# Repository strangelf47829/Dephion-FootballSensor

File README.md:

# Dephion FootballSensor
 
NOT IN PUBLIC DOMAIN!!!!

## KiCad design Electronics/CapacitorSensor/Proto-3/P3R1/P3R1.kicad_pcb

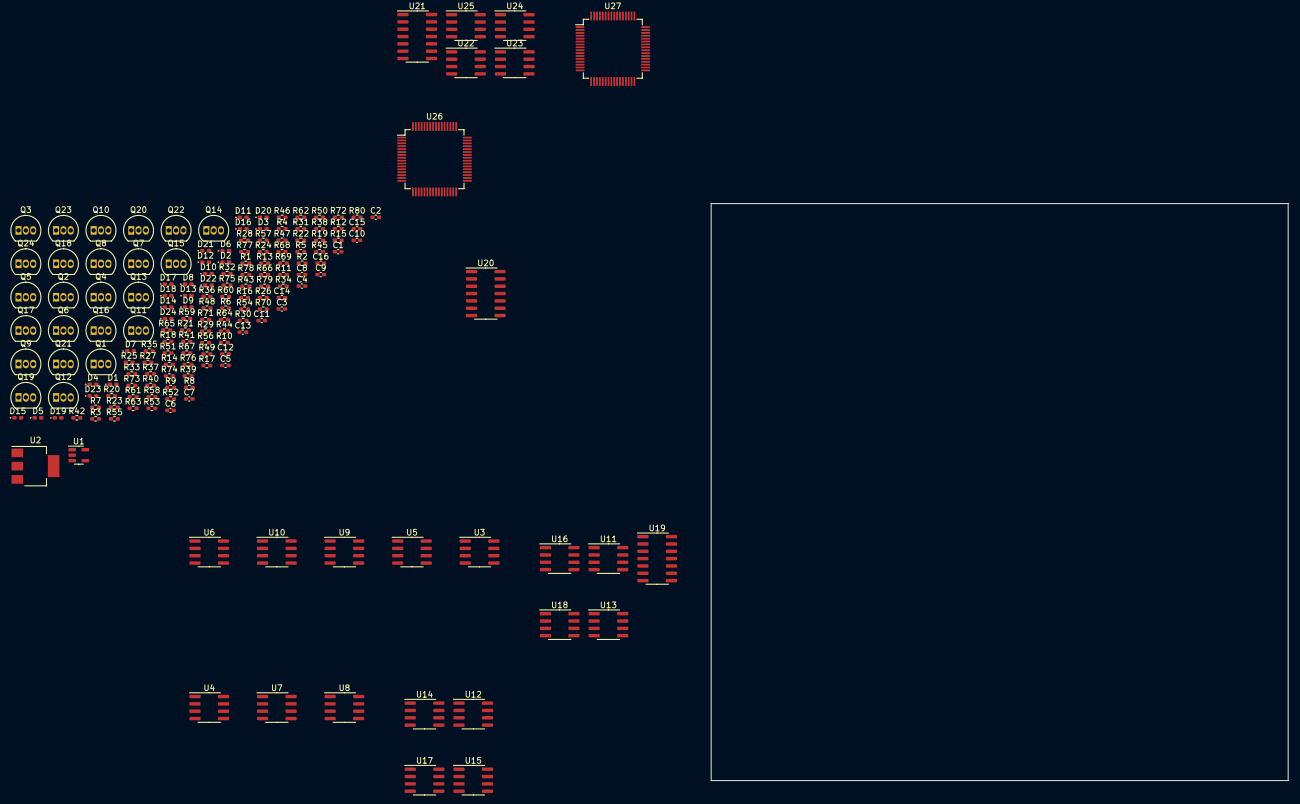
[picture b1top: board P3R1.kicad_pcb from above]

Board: 2 copper layers, 100.0 x 100.0 mm, 171 parts (0 on the bottom side), 124 nets, no tracks yet.

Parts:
C1, C2, C3, C4, C5, C6, C7, C8, C9, C10, C11, C12, C13, C14, C15, C16: C; C_0402_1005Metric_Pad0.74x0.62mm_HandSolder
D1, D2, D3, D4, D5, D6, D7, D8, D9, D10, D11, D12, D13, D14, D15, D16, D17, D18, D19, D20, D21, D22, D23, D24: D; D_0402_1005Metric_Pad0.77x0.64mm_HandSolder
Q1, Q2, Q3, Q4, Q5, Q6, Q7, Q8, Q17, Q18, Q19, Q20, Q21, Q22, Q23, Q24: BC547; TO-92_Inline
Q9, Q10, Q11, Q12, Q13, Q14, Q15, Q16: BS107; TO-92_Inline
R1, R2, R3, R4, R5, R6, R7, R8, R9, R10, R11, R12, R13, R14, R15, R16, R17, R18, R19, R20, R21, R22, R23, R24, R25, R26, R27, R28, R29, R30, R31, R32, R33, R34, R35, R36, R37, R38, R39, R40, R41, R42, R43, R44, R45, R46, R47, R48, R49, R50, R51, R52, R53, R54, R55, R56, R57, R58, R59, R60, R61, R62, R63, R64, R65, R66, R67, R68, R69, R70, R71, R72, R73, R74, R75, R76, R77, R78, R79, R80: R; R_0402_1005Metric_Pad0.72x0.64mm_HandSolder
U1: TC2185-2.8VxCTTR; SOT-23-5
U2: AMS1117-5.0; SOT-223-3_TabPin2
U3, U4, U5, U6, U7, U8, U9, U10, U11, U12, U13, U14, U15, U16, U17, U18: LM318N; SOIC-8_3.9x4.9mm_P1.27mm
U19, U20, U21: 74LS14; SOIC-14_3.9x8.7mm_P1.27mm
U22, U23, U24, U25: LM393; SOIC-8_3.9x4.9mm_P1.27mm
U26, U27: STM32L431RCTx; LQFP-64_10x10mm_P0.5mm

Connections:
+2V8: R42.1, R44.1, R46.1, R48.1, R50.1, R52.1, R54.1, R56.1
+5V: U22.8 (V+), U23.8 (V+), U24.8 (V+), U25.8 (V+)
B0: Q1.3 (E), Q9.1 (D), Q17.3 (E), R41.2, U3.3 (+), U3.4 (V-), U11.4 (V-)
B1: Q2.3 (E), Q10.1 (D), Q18.3 (E), R43.2, U4.3 (+), U4.4 (V-), U12.4 (V-)
B2: Q3.3 (E), Q11.1 (D), Q19.3 (E), R45.2, U5.3 (+), U5.4 (V-), U13.4 (V-)
B3: Q4.3 (E), Q12.1 (D), Q20.3 (E), R47.2, U6.3 (+), U6.4 (V-), U14.4 (V-)
B4: Q5.3 (E), Q13.1 (D), Q21.3 (E), R49.2, U7.3 (+), U7.4 (V-), U15.4 (V-)
B5: Q6.3 (E), Q14.1 (D), Q22.3 (E), R51.2, U8.3 (+), U8.4 (V-), U16.4 (V-)
B6: Q7.3 (E), Q15.1 (D), Q23.3 (E), R53.2, U9.3 (+), U9.4 (V-), U17.4 (V-)
B7: Q8.3 (E), Q16.1 (D), Q24.3 (E), R55.2, U10.3 (+), U10.4 (V-), U18.4 (V-)
C0: D1.2 (A), R1.1
C1: D2.2 (A), R2.1
C2: D3.2 (A), R3.1
C3: D4.2 (A), R4.1
C4: D5.2 (A), R5.1
C5: D6.2 (A), R6.1
C6: D7.2 (A), R7.1
C7: D8.2 (A), R8.1
G0: D1.1 (K), D9.2 (A)
G1: D2.1 (K), D10.2 (A)
G2: D3.1 (K), D11.2 (A)
G3: D4.1 (K), D12.2 (A)
G4: D5.1 (K), D13.2 (A)
G5: D6.1 (K), D14.2 (A)
G6: D7.1 (K), D15.2 (A)
G7: D8.1 (K), D16.2 (A)
GNDA: U22.3 (+), U22.4 (V-), U22.5 (+), U23.3 (+), U23.4 (V-), U23.5 (+), U24.3 (+), U24.4 (V-), U24.5 (+), U25.3 (+), U25.4 (V-), U25.5 (+)
unnamed: C1.1, R25.2
unnamed: C1.2, C9.2, R33.1, U3.2 (-)
unnamed: C2.1, R26.2
unnamed: C3.1, R27.2
unnamed: C4.1, R28.2
unnamed: C5.1, R29.2
unnamed: C6.1, R30.2
unnamed: C7.1, R31.2
unnamed: C8.1, R32.2
unnamed: C9.1, D17.1 (K), R33.2, R65.2
unnamed: C10.1, D18.1 (K), R34.2, R66.2, U4.8 (BAL2)
unnamed: C2.2, C10.2, R34.1, U4.2 (-)
unnamed: C11.1, D19.1 (K), R35.2, R67.2, U5.8 (BAL2)
unnamed: C3.2, C11.2, R35.1, U5.2 (-)
unnamed: C12.1, D20.1 (K), R36.2, R68.2, U6.8 (BAL2)
unnamed: C4.2, C12.2, R36.1, U6.2 (-)
unnamed: C13.1, D21.1 (K), R37.2, R69.2, U7.8 (BAL2)
unnamed: C5.2, C13.2, R37.1, U7.2 (-)
unnamed: C14.1, D22.1 (K), R38.2, R70.2, U8.8 (BAL2)
unnamed: C6.2, C14.2, R38.1, U8.2 (-)
unnamed: C15.1, D23.1 (K), R39.2, R71.2, U9.8 (BAL2)
unnamed: C7.2, C15.2, R39.1, U9.2 (-)
unnamed: C16.1, D24.1 (K), R40.2, R72.2, U10.8 (BAL2)
unnamed: C8.2, C16.2, R40.1, U10.2 (-)
unnamed: D9.1 (K), R17.1
unnamed: D10.1 (K), R18.1
unnamed: D11.1 (K), R19.1
unnamed: D12.1 (K), R20.1
unnamed: D13.1 (K), R21.1
unnamed: D14.1 (K), R22.1
unnamed: D15.1 (K), R23.1
unnamed: D16.1 (K), R24.1
unnamed: D17.2 (A), Q17.1 (C), R73.2, U11.6, U19.1
unnamed: D18.2 (A), Q18.1 (C), R74.2, U12.6, U19.5
unnamed: D19.2 (A), Q19.1 (C), R75.2, U13.6, U19.11
unnamed: D20.2 (A), Q20.1 (C), R76.2, U14.6, U20.1
unnamed: D21.2 (A), Q21.1 (C), R77.2, U15.6, U20.5
unnamed: D22.2 (A), Q22.1 (C), R78.2, U16.6, U20.11
unnamed: D23.2 (A), Q23.1 (C), R79.2, U17.6, U21.1
unnamed: D24.2 (A), Q24.1 (C), R80.2, U18.6, U21.5
unnamed: Q1.1 (C), Q9.2 (G), R9.2
unnamed: Q1.2 (B), R1.2
unnamed: Q2.2 (B), R2.2
unnamed: Q3.2 (B), R3.2
unnamed: Q4.2 (B), R4.2
unnamed: Q5.2 (B), R5.2
unnamed: Q6.2 (B), R6.2
unnamed: Q7.2 (B), R7.2
unnamed: Q8.2 (B), R8.2
unnamed: Q9.3 (S), R17.2, R25.1
unnamed: Q2.1 (C), Q10.2 (G), R10.2
unnamed: Q10.3 (S), R18.2, R26.1
unnamed: Q3.1 (C), Q11.2 (G), R11.2
unnamed: Q11.3 (S), R19.2, R27.1
unnamed: Q4.1 (C), Q12.2 (G), R12.2
unnamed: Q12.3 (S), R20.2, R28.1
unnamed: Q5.1 (C), Q13.2 (G), R13.2
unnamed: Q13.3 (S), R21.2, R29.1
unnamed: Q6.1 (C), Q14.2 (G), R14.2
unnamed: Q14.3 (S), R22.2, R30.1
unnamed: Q7.1 (C), Q15.2 (G), R15.2
unnamed: Q15.3 (S), R23.2, R31.1
unnamed: Q8.1 (C), Q16.2 (G), R16.2
unnamed: Q16.3 (S), R24.2, R32.1
unnamed: R41.1, R42.2, R57.1
unnamed: R43.1, R44.2, R58.1
unnamed: R45.1, R46.2, R59.1
unnamed: R47.1, R48.2, R60.1
unnamed: R49.1, R50.2, R61.1
unnamed: R51.1, R52.2, R62.1
unnamed: R53.1, R54.2, R63.1
unnamed: R55.1, R56.2, R64.1
unnamed: R57.2, R73.1
unnamed: R58.2, R74.1
unnamed: R59.2, R75.1
unnamed: R60.2, R76.1
unnamed: R61.2, R77.1
unnamed: R62.2, R78.1
unnamed: R63.2, R79.1
unnamed: R64.2, R80.1
unnamed: R65.1, U11.3 (+)
unnamed: R66.1, U12.3 (+)
unnamed: R67.1, U13.3 (+)
unnamed: R68.1, U14.3 (+)
unnamed: R69.1, U15.3 (+)
unnamed: R70.1, U16.3 (+)
unnamed: R71.1, U17.3 (+)
unnamed: R72.1, U18.3 (+)
unnamed: U19.2, U19.3
unnamed: U19.6, U19.9
unnamed: U19.10, U19.13
unnamed: U20.2, U20.3
unnamed: U20.6, U20.9
unnamed: U20.10, U20.13
unnamed: U21.2, U21.3
unnamed: U21.6, U21.9
VCC: R9.1, R10.1, R11.1, R12.1, R13.1, R14.1, R15.1, R16.1, U3.7 (V+), U4.7 (V+), U5.7 (V+), U6.7 (V+), U7.7 (V+), U8.7 (V+), U9.7 (V+), U10.7 (V+), U11.7 (V+), U12.7 (V+), U13.7 (V+), U14.7 (V+), U15.7 (V+), U16.7 (V+), U17.7 (V+), U18.7 (V+)

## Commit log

2022-09-25 Some misc file management
2022-09-28 Added old measurements and first schematic revision.
    A new revision is currently being made, along with a frequency response analysis. Current measurements show the best frequency to be 11.8 MHz
2022-10-06 P1R2 and P2R1 added
2022-10-06 Decided to continue work on other laptop. Added forgotten resistor to P2R1
2022-10-06 Barebones image for Raspi Made
2022-10-06 Updated stuff
2022-10-11 a lot of work went into this
2022-10-11 Moare
2022-10-18 Made some stuff
    :)
2022-10-18 SDL2 added
2022-10-19 Started making the BBP3 Devboard
2022-10-19 Gewerkt aan Camera
2022-10-19 Test
2022-11-03 Dont delete this
    you got me???
